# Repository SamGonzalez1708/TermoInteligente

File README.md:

# TermoInteligente
### Integrantes
- Samuel Alejandro Gonzalez Herrera.
- Daniel Alejandro Guevara Garavito.

# Introducción
A la hora de saber cual es la temperatura de las bebidas que consumimos en nuestra cotidianidad, no hay muchas herramientas que faciliten la precisión de estos datos, y en muchas ocasiones es importante tener presente cual es la temperatura de los líquidos que consumimos, ya sea que se quiera garantizar temperaturas adecuadas para la seguridad humana, o simplemente se quiera cocinar adecuadamente algo. Es por esto que se desarrollo un termo inteligente, capaz de leer la temperatura del liquido y mostrar mediante una pantalla al usuario, a que temperatura se encuentra, ademas de avisar mediante un buzzer cuando la temperatura del liquido implique un peligro al usuario.

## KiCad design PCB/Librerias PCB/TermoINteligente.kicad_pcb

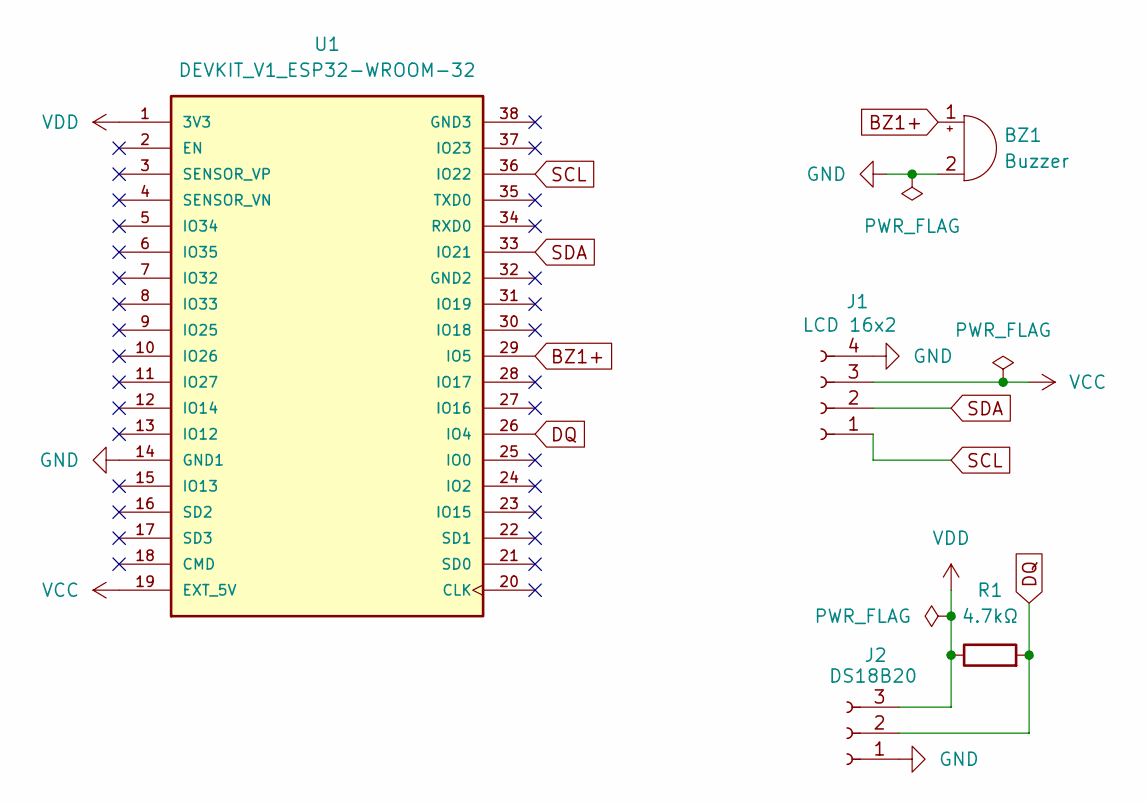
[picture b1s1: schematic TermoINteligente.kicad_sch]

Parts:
BZ1: Buzzer; Buzzer_12x9.5RM7.6
J1: LCD 16x2; PinSocket_1x04_P2.54mm_Vertical
J2: DS18B20; PinSocket_1x03_P2.54mm_Vertical
R1: 4.7kΩ; R_Axial_DIN0207_L6.3mm_D2.5mm_P10.16mm_Horizontal
U1: DEVKIT_V1_ESP32-WROOM-32; MODULE_DEVKIT_V1_ESP32-WROOM-32; PARTREV N/A

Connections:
BZ1+: BZ1.1 (+), U1.29 (IO5)
DQ: J2.2, R1.2, U1.26 (IO4)
GND: BZ1.2 (-), J1.4, J2.1, U1.14 (GND1)
SCL: J1.1, U1.36 (IO22)
SDA: J1.2, U1.33 (IO21)
VCC: J1.3, U1.19 (EXT_5V)
VDD: J2.3, R1.1, U1.1 (3V3)

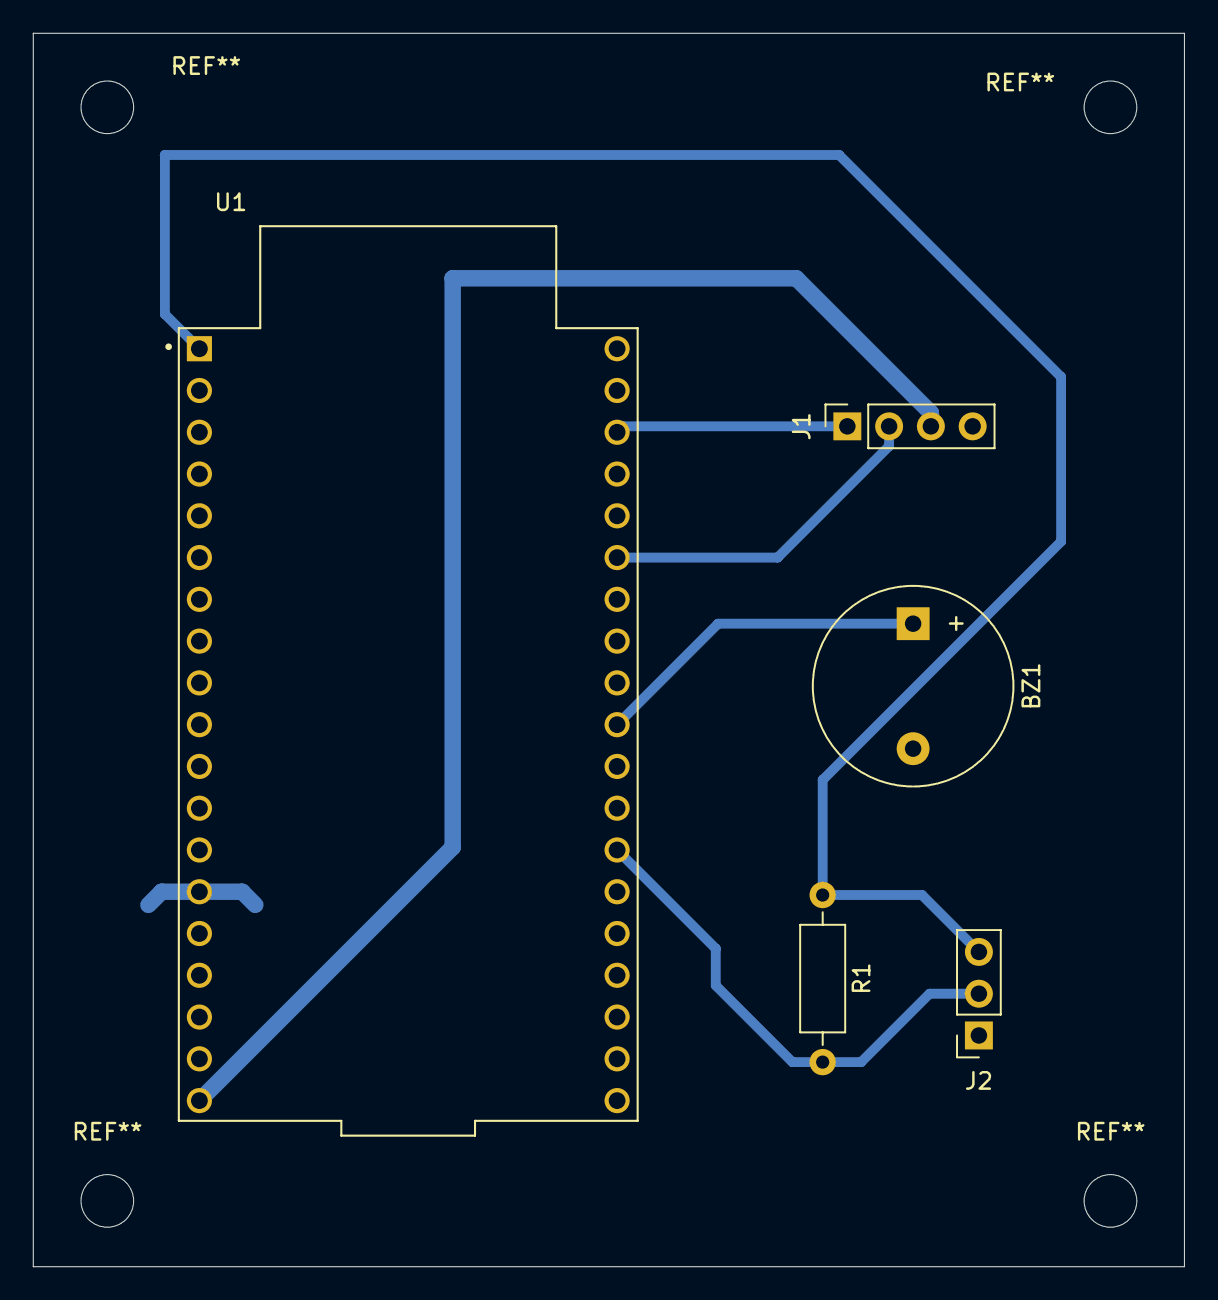
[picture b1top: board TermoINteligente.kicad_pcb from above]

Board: 2 copper layers, 70.0 x 75.0 mm, 5 parts (0 on the bottom side), 7 nets.

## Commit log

2025-03-04 Diagramas
2025-03-04 Create temp
2025-03-05 Rename Diapositiva1.PNG to Poster.PNG
2025-03-05 Rename WhatsApp Image 2025-03-04 at 8.59.00 PM.jpeg to Evidencia Sensor DS18B20.jpeg
2025-03-05 Rename WhatsApp Image 2025-03-04 at 9.01.10 PM.jpeg to Evidencia Sensor DS18B20 y Buzzer.jpeg
2025-03-06 Rename WhatsApp Image 2025-03-05 at 8.47.07 PM (1).jpeg to Vista Trasera PCB con Componentes.jpeg
2025-03-06 Rename WhatsApp Image 2025-03-05 at 8.47.07 PM.jpeg to Vista PCB con Componentes.jpeg
2025-03-06 Rename WhatsApp Image 2025-03-05 at 8.49.29 PM.jpeg to PCB Frontal.jpeg
2025-03-06 Rename WhatsApp Image 2025-03-05 at 8.49.30 PM.jpeg to PCB Trasera.jpeg
